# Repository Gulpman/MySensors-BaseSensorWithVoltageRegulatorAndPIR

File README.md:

# MySensors-BaseSensorWithVoltageRegulatorAndPIR
A battery powerd (CR123A) basic sensor with onboard PIR mounting and voltage regulator to 3.3V

This is my first own eagle project.

<h1>What's on the sensor?</h1>
<ul>
<li>ATMega 328P-AU</li>
<li>NRF24L01+ SMD version</li>
<li>AT25DF512C-SSHN-B EEPROM (512k) (optional)</li>
<li>ATSHA204A (optional)</li>
<li>PIR Sensor 3.3V (optional)</li>
<li>MAX1724+ (optional - if you do not want to use it shorten jumper SJ2)</li>
<li>I2C header with (optional) Pullups</li>
	<ul>
        <li>PIN layout allows to directly connect standard breakout boards for BMPx80 or Si7021</li>
    </ul>
<li>FTDI header</li>
	<ul>
        <li>As I used the Sparkfun headers the FTDI header can just be pulled in and does not have to be soldered (hopefully, never tried it out :) )</li>
    </ul>
<li>ISP header</li>
<li>CR123A battery holder</li>
<li>The following pins can be used via pin headers</li>
    <ul>
        <li>A1 to A2</li>
        <li>D3 to D6</li>
    </ul>
</ul>

Jumper SJ1 is useless at the moment - the idea behind it is that, dependent on the battery level the SHDN pin of the MAX 1724 could be set to low or high by the sketch running on the 328P. Help and hints for implementing this are highly appreciated. :)

The PCB is meant to fit into an ABS82 case. The ABS-82 is for example available at TME -> <a href="http://www.tme.eu/de/details/abs-82/universal-gehaeuse/">ABS-82 @ TME</a>. 

Big kudos go to Omega-5 from forum.fhem.de who had an eye on my first steps in the Eagle world and who is responsible at least for a few of the capacitors and their position very close to the 328P :)
I think I can admit that this sensor would have had no chance to function without him having a look on my files.

After the sensor has proven that it is functioning the next version will have the following improvements:
<ul>
<li>Smaller - PIR sensor will not be mounted onboard. Makes it cheaper to produce as well as more flexible.</li>
<li>Implementation of SJ1 - allow the sketch to shutdown the MAX 1724 if voltage of the battery is high enough.</li>
<li>Optional pullups for digital and anolog pins</li>
</ul>

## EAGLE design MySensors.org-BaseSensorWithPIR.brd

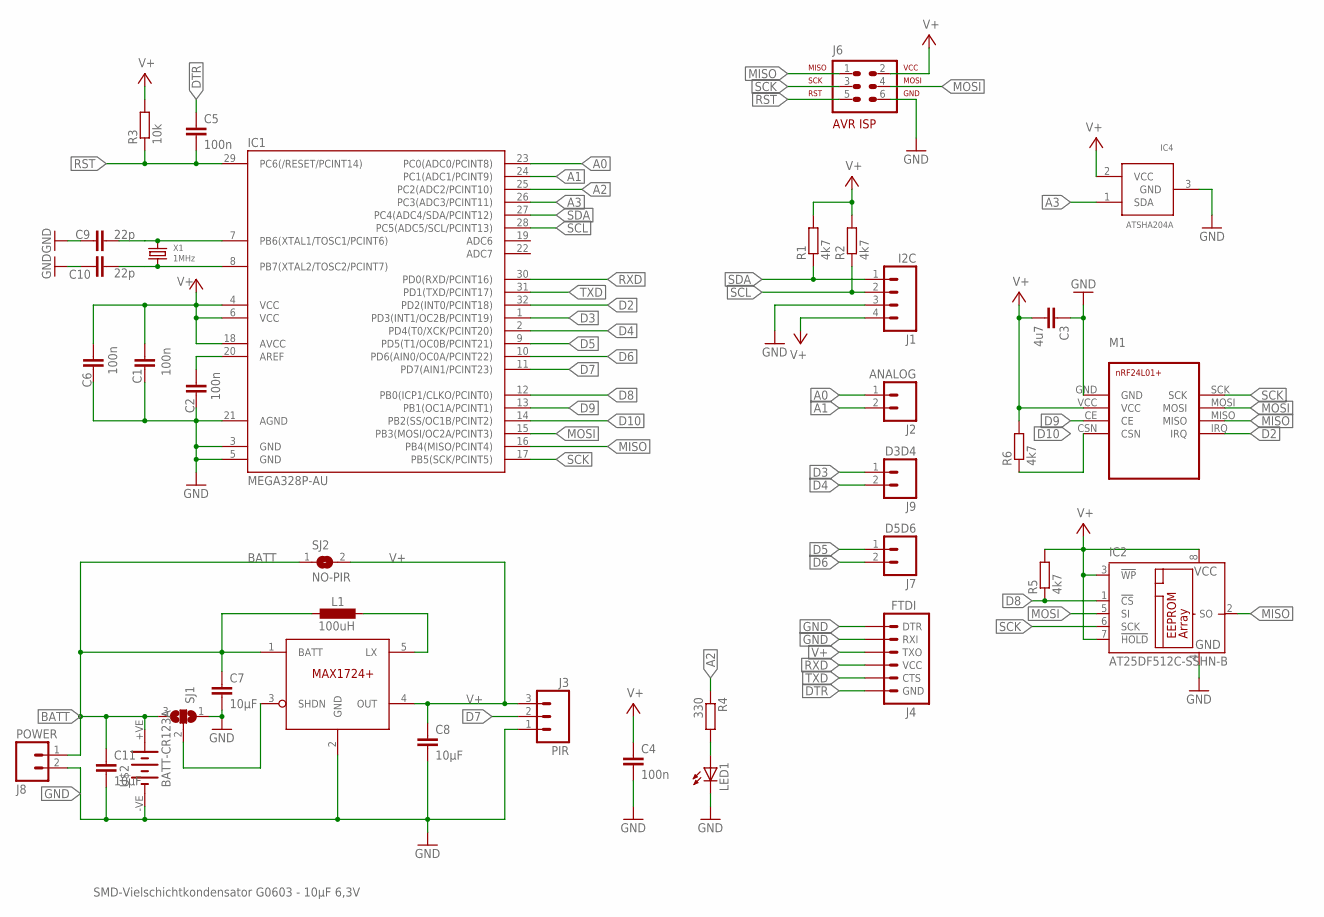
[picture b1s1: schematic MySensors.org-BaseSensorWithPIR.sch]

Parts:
C1, C2, C4, C5, C6: 100n; C0603
C3: 4u7; C0603
C7, C8, C11: 10µF; C0603
C9, C10: 22p; C0603
IC1: MEGA328P-AU; TQFP32-08
IC2: AT25DF512C-SSHN-B; SO-08
IC4: ATSHA204A; SOT23
J1: I2C; 1X04_LOCK
J2: ANALOG; 1X02
J3: PIR; 1X03_LOCK
J4: FTDI; 1X06_LOCK
J6: N/M; AVR-ISP-6
J7: D5D6; 1X02
J8: POWER; 1X02
J9: D3D4; 1X02
L1: 100uH; 1212FPS
LED1: LEDSML0603; SML0603
M1: NRF24L01+NRF24L01+MINI; NRF24L01+MINI
R1, R2, R5, R6: 4k7; R0603
R3: 10k; R0603
R4: 330; R0603
SJ1: SJ2W; SJ_2
SJ2: NO-PIR; SJ
STEPUP: MAX1724; SOT23-5L
U$2: BATT-CR123A; KEYSTONE-2/3A
X1: 1MHz; 2P-L3.2XW1.5MM

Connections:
A0: IC1.23 (PC0(ADC0/PCINT8)), J2.1
A1: IC1.24 (PC1(ADC1/PCINT9)), J2.2
A2: IC1.25 (PC2(ADC2/PCINT10)), R4.1
A3: IC1.26 (PC3(ADC3/PCINT11)), IC4.1 (SDA)
BATT: C7.1, C11.1, J8.1, L1.1, SJ1.3, SJ2.1, STEPUP.1 (BATT), U$2.+VE (+)
D2: IC1.32 (PD2(INT0/PCINT18)), M1.IRQ
D3: IC1.1 (PD3(INT1/OC2B/PCINT19)), J9.1
D4: IC1.2 (PD4(T0/XCK/PCINT20)), J9.2
D5: IC1.9 (PD5(T1/OC0B/PCINT21)), J7.1
D6: IC1.10 (PD6(AIN0/OC0A/PCINT22)), J7.2
D7: IC1.11 (PD7(AIN1/PCINT23)), J3.2
D8: IC1.12 (PB0(ICP1/CLKO/PCINT0)), IC2.1 (!CS), R5.1
D9: IC1.13 (PB1(OC1A/PCINT1)), M1.CE
D10: IC1.14 (PB2(SS/OC1B/PCINT2)), M1.CSN, R6.1
DTR: C5.1, J4.6 (GND)
GND: C1.2, C2.2, C3.1, C4.2, C6.2, C7.2, C8.2, C9.2, C10.2, C11.2, IC1.3 (GND), IC1.5 (GND), IC1.21 (AGND), IC2.4 (GND), IC4.3 (GND), J1.3, J3.1, J4.1 (DTR), J4.2 (RXI), J6.6, J8.2, LED1.C, M1.GND, SJ1.1, STEPUP.2 (GND), U$2.-VE (-)
LX: L1.2, STEPUP.5 (LX)
MISO: IC1.16 (PB4(MISO/PCINT4)), IC2.2 (SO), J6.1, M1.MISO
MOSI: IC1.15 (PB3(MOSI/OC2A/PCINT3)), IC2.5 (SI), J6.4, M1.MOSI
unnamed: LED1.A, R4.2
unnamed: C2.1, IC1.20 (AREF)
RST: C5.2, IC1.29 (PC6(/RESET/PCINT14)), J6.5, R3.1
RXD: IC1.30 (PD0(RXD/PCINT16)), J4.4 (VCC)
SCK: IC1.17 (PB5(SCK/PCINT5)), IC2.6 (SCK), J6.3, M1.SCK
SCL: IC1.28 (PC5(ADC5/SCL/PCINT13)), J1.2, R2.1
SDA: IC1.27 (PC4(ADC4/SDA/PCINT12)), J1.1, R1.1
SHDN: SJ1.2, STEPUP.3 (SHDN)
TXD: IC1.31 (PD1(TXD/PCINT17)), J4.5 (CTS)
V+: C1.1, C3.2, C4.1, C6.1, C8.1, IC1.4 (VCC), IC1.6 (VCC), IC1.18 (AVCC), IC2.3 (!WP), IC2.7 (!HOLD), IC2.8 (VCC), IC4.2 (VCC), J1.4, J3.3, J4.3 (TXO), J6.2, M1.VCC, R1.2, R2.2, R3.2, R5.2, R6.2, SJ2.2, STEPUP.4 (OUT)
XTAL1: C9.1, IC1.7 (PB6(XTAL1/TOSC1/PCINT6)), X1.2
XTAL2: C10.1, IC1.8 (PB7(XTAL2/TOSC2/PCINT7)), X1.1

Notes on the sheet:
SMD-Vielschichtkondensator G0603 - 10µF 6,3V

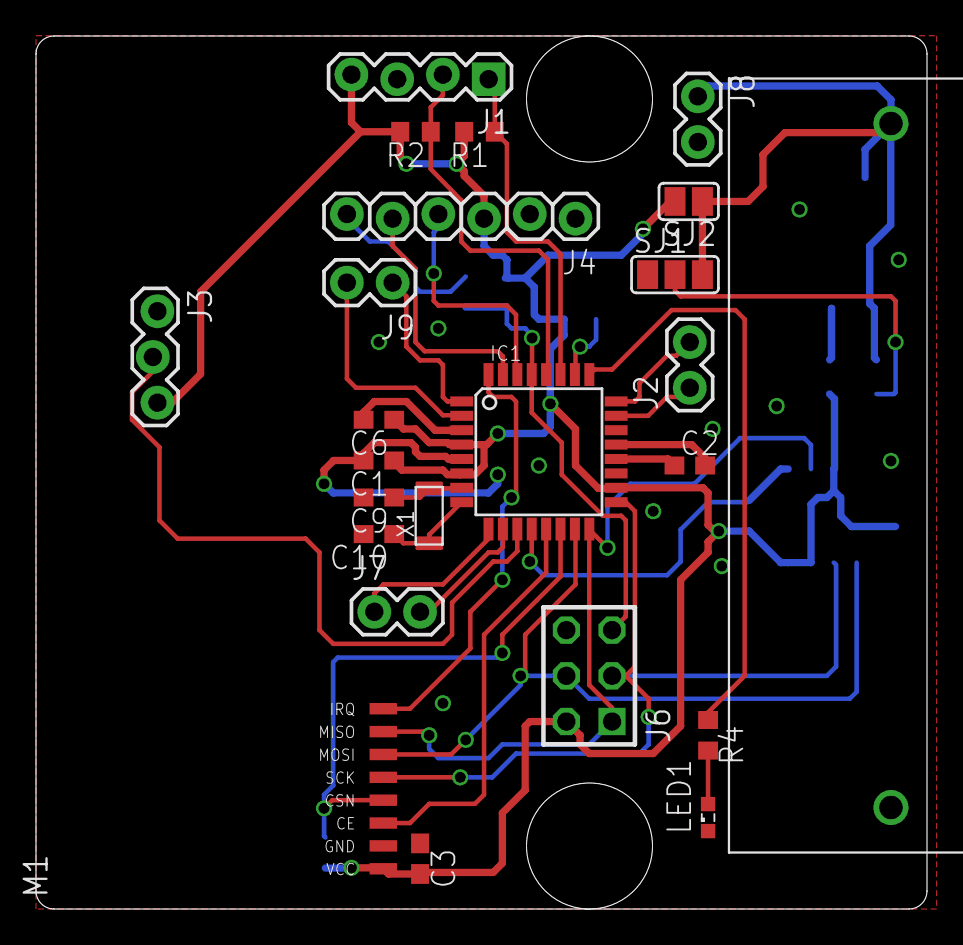
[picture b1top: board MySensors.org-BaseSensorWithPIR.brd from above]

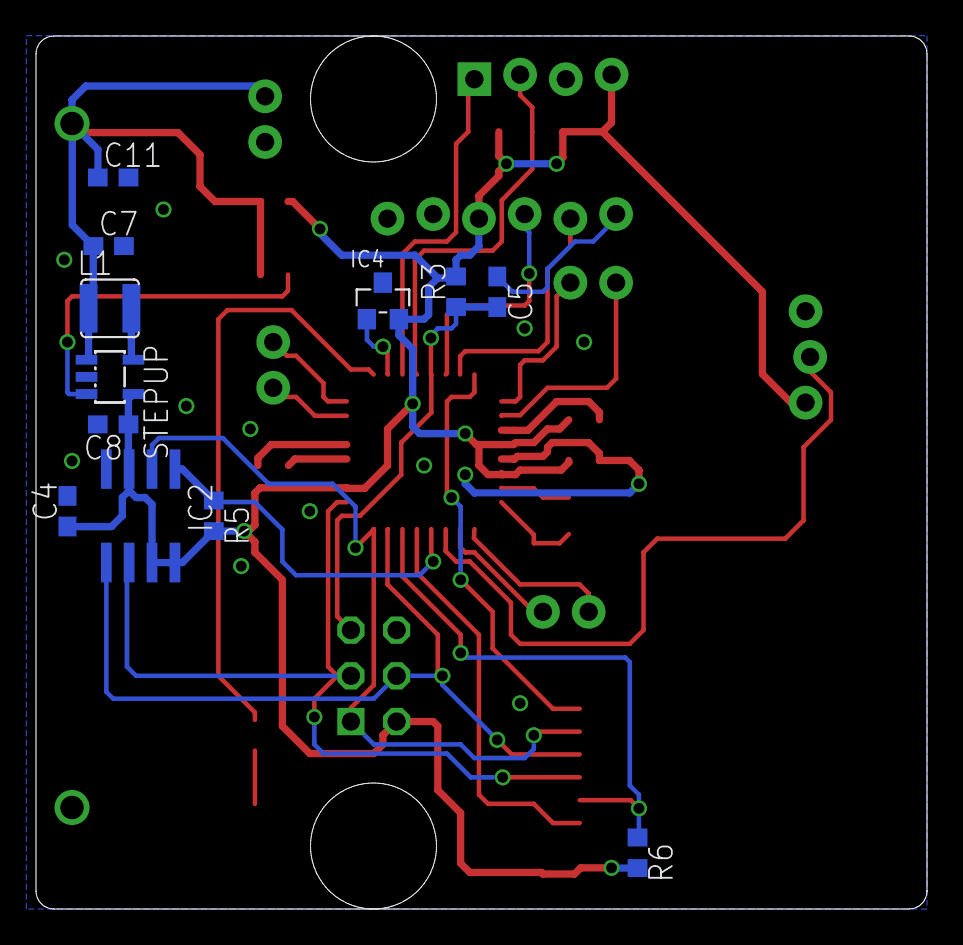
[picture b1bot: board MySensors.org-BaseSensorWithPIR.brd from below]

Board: 2 copper layers, 49.5 x 48.5 mm, 36 parts (12 on the bottom side), 31 nets.

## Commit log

2016-03-29 Added Eagle Schematics and Board
2016-04-01 - some aesthetic corrections in the schema: - positive voltages are now all alligned upright - D10 label is directly connected to the electrical wire (there was a space in between before)

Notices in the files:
parts and their libraries:
SparkFun-Connectors: Licensing: Creative Commons ShareAlike 4.0 International - https://creativecommons.org/licenses/by-sa/4.0
